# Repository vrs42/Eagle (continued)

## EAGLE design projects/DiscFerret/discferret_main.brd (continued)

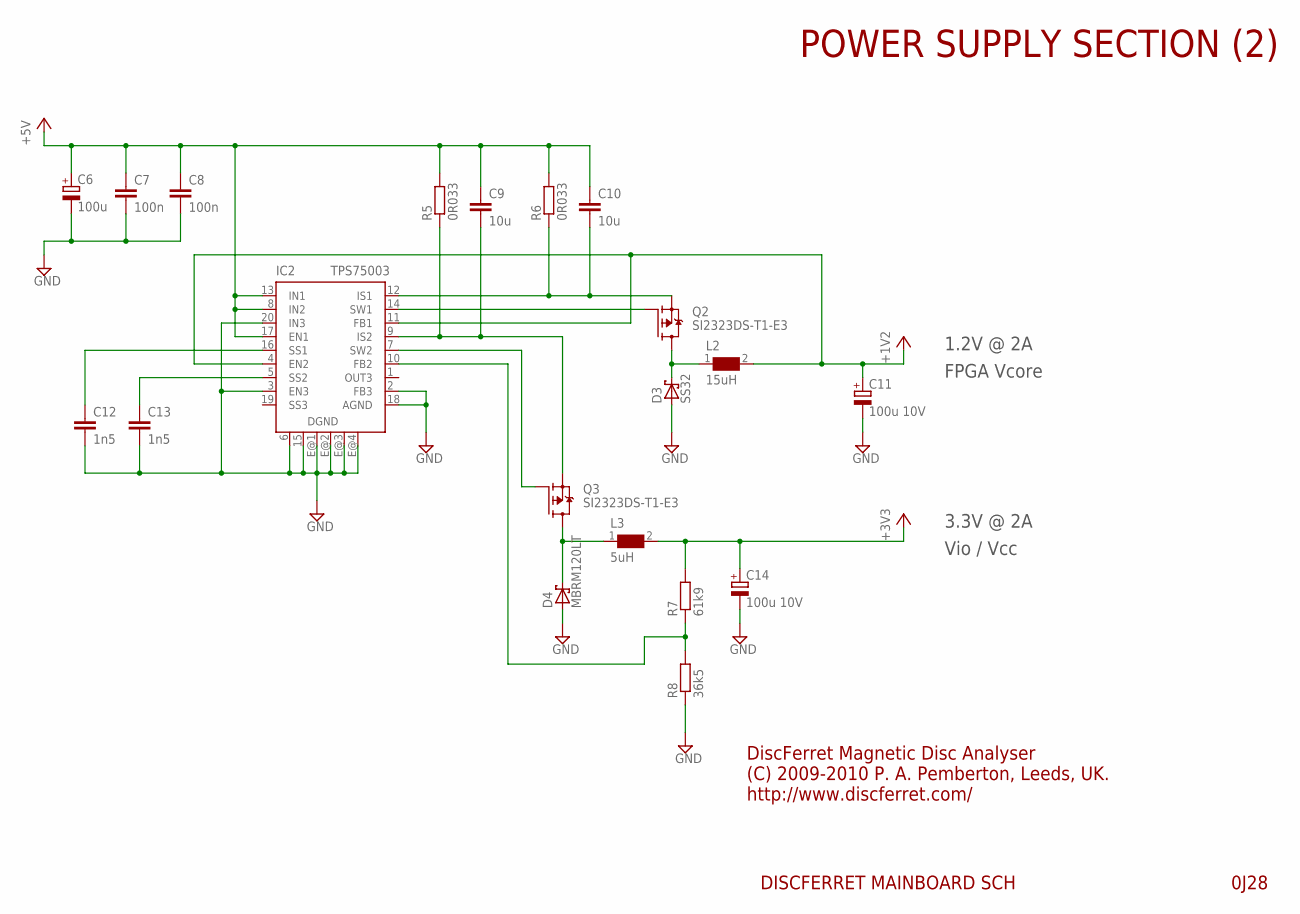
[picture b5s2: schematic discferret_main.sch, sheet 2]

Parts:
C6: 100u; SMC_D
C7, C8: 100n; C0805
C9, C10: 10u; C0805
C11, C14: 100u 10V; SMC_D
C12, C13: 1n5; C0805
D3: SS32; SMC
D4: MBRM120LT; POWERMITE_LARGEPAD
IC2: TPS75003; R-PQFP-N20
L2: 15uH; WE-TPC_XL/XLH
L3: 5uH; WE-TPC_XL/XLH
Q2, Q3: SI2323DS-T1-E3; SOT23
R5, R6: 0R033; R1206
R7: 61k9; R0805
R8: 36k5; R0603

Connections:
+1V2: C11.+, IC2.4 (EN2), IC2.11 (FB1), L2.2; also elsewhere on the board
+3V3: C14.+, L3.2, R7.2; also elsewhere on the board
+5V: C6.+, C7.1, C8.1, C9.1, C10.1, IC2.8 (IN2), IC2.13 (IN1), IC2.17 (EN1), R5.2, R6.2; also elsewhere on the board
GND: C6.-, C7.2, C8.2, C11.-, C12.2, C13.2, C14.-, D3.A, D4.2 (A), IC2.2 (FB3), IC2.3 (EN3), IC2.6 (DGND), IC2.15 (DGND), IC2.18 (AGND), IC2.20 (IN3), IC2.E@1 (DGND), IC2.E@2 (DGND), IC2.E@3 (DGND), IC2.E@4 (DGND), R8.1; also elsewhere on the board
unnamed: C9.2, IC2.9 (IS2), Q3.2 (S), R5.1
unnamed: C12.1, IC2.16 (SS1)
unnamed: C13.1, IC2.5 (SS2)
unnamed: C10.2, IC2.12 (IS1), Q2.2 (S), R6.1
unnamed: IC2.14 (SW1), Q2.1 (G)
unnamed: IC2.7 (SW2), Q3.1 (G)
unnamed: D3.C, L2.1, Q2.3 (D)
unnamed: D4.1 (C), L3.1, Q3.3 (D)
unnamed: IC2.10 (FB2), R7.1, R8.2

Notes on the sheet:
DiscFerret Magnetic Disc Analyser
0J28
DISCFERRET MAINBOARD SCH
(C) 2009-2010 P. A. Pemberton, Leeds, UK.
http://www.discferret.com/
POWER SUPPLY SECTION (2)
1.2V @ 2A
3.3V @ 2A
FPGA Vcore
Vio / Vcc

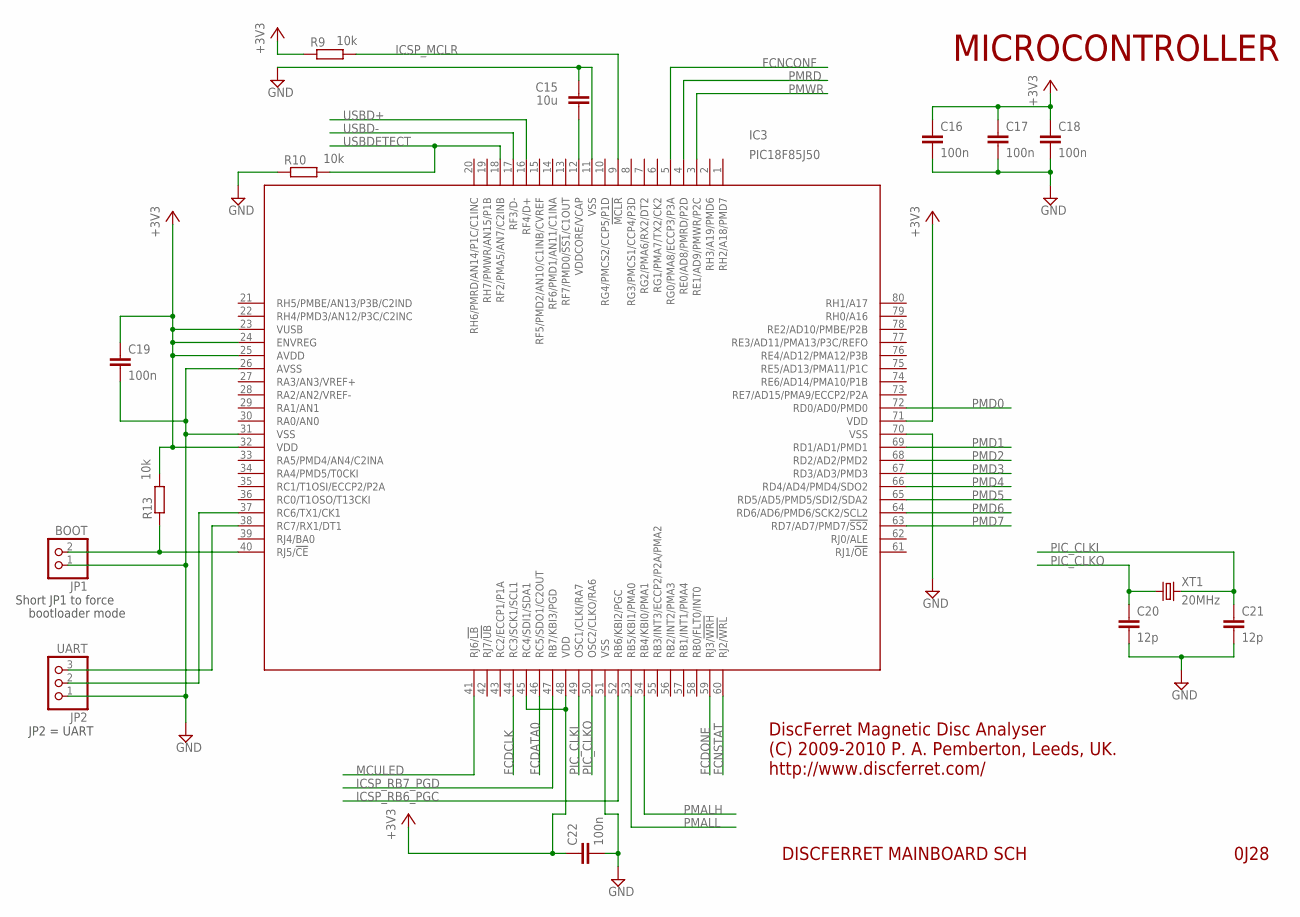
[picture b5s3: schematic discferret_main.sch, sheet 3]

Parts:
C15: 10u; C0805
C16, C17, C18, C19, C22: 100n; C0603
C20, C21: 12p; C0603
IC3: PIC18F85J50; TQFP80-12X12
JP1: BOOT; 1X02
JP2: UART; 1X03
R9, R10, R13: 10k; R0805
XT1: 20MHz; HC49/S

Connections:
+3V3: C16.1, C17.1, C18.1, C19.1, C22.1, IC3.23 (VUSB), IC3.24 (ENVREG), IC3.25 (AVDD), IC3.32 (VDD), IC3.45 (RC4/SDI1/SDA1), IC3.48 (VDD), IC3.71 (VDD), R9.1, R13.2; also elsewhere on the board
FCDATA0: IC3.46 (RC5/SDO1/C2OUT); also elsewhere on the board
FCDCLK: IC3.44 (RC3/SCK1/SCL1); also elsewhere on the board
FCDONE: IC3.59 (RJ3/!WRH); also elsewhere on the board
FCNCONF: IC3.5 (RG0/PMA8/ECCP3/P3A); also elsewhere on the board
FCNSTAT: IC3.60 (RJ2/!WRL); also elsewhere on the board
GND: C15.1, C16.2, C17.2, C18.2, C19.2, C20.2, C21.2, C22.2, IC3.11 (VSS), IC3.26 (AVSS), IC3.31 (VSS), IC3.51 (VSS), IC3.70 (VSS), JP1.1, JP2.1, R10.1; also elsewhere on the board
ICSP_MCLR: IC3.9 (!MCLR), R9.2; also elsewhere on the board
ICSP_RB6_PGC: IC3.52 (RB6/KBI2/PGC); also elsewhere on the board
ICSP_RB7_PGD: IC3.47 (RB7/KBI3/PGD); also elsewhere on the board
MCULED: IC3.41 (RJ6/!LB); also elsewhere on the board
unnamed: IC3.40 (RJ5/!CE), JP1.2, R13.1
unnamed: C15.2, IC3.12 (VDDCORE/VCAP)
unnamed: IC3.37 (RC6/TX1/CK1), JP2.2
unnamed: IC3.38 (RC7/RX1/DT1), JP2.3
PIC_CLKI: C21.1, IC3.49 (OSC1/CLKI/RA7), XT1.2
PIC_CLKO: C20.1, IC3.50 (OSC2/CLKO/RA6), XT1.1
PMALH: IC3.54 (RB4/KBI0/PMA1); also elsewhere on the board
PMALL: IC3.53 (RB5/KBI1/PMA0); also elsewhere on the board
PMD0: IC3.72 (RD0/AD0/PMD0); also elsewhere on the board
PMD1: IC3.69 (RD1/AD1/PMD1); also elsewhere on the board
PMD2: IC3.68 (RD2/AD2/PMD2); also elsewhere on the board
PMD3: IC3.67 (RD3/AD3/PMD3); also elsewhere on the board
PMD4: IC3.66 (RD4/AD4/PMD4/SDO2); also elsewhere on the board
PMD5: IC3.65 (RD5/AD5/PMD5/SDI2/SDA2); also elsewhere on the board
PMD6: IC3.64 (RD6/AD6/PMD6/SCK2/SCL2); also elsewhere on the board
PMD7: IC3.63 (RD7/AD7/PMD7/!SS2); also elsewhere on the board
PMRD: IC3.4 (RE0/AD8/PMRD/P2D); also elsewhere on the board
PMWR: IC3.3 (RE1/AD9/PMWR/P2C); also elsewhere on the board
USBD+: IC3.16 (RF4/D+); also elsewhere on the board
USBD-: IC3.17 (RF3/D-); also elsewhere on the board
USBDETECT: IC3.18 (RF2/PMA5/AN7/C2INB), R10.2; also elsewhere on the board

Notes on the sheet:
DiscFerret Magnetic Disc Analyser
0J28
DISCFERRET MAINBOARD SCH
(C) 2009-2010 P. A. Pemberton, Leeds, UK.
http://www.discferret.com/
MICROCONTROLLER
Short JP1 to force
bootloader mode
JP2 = UART

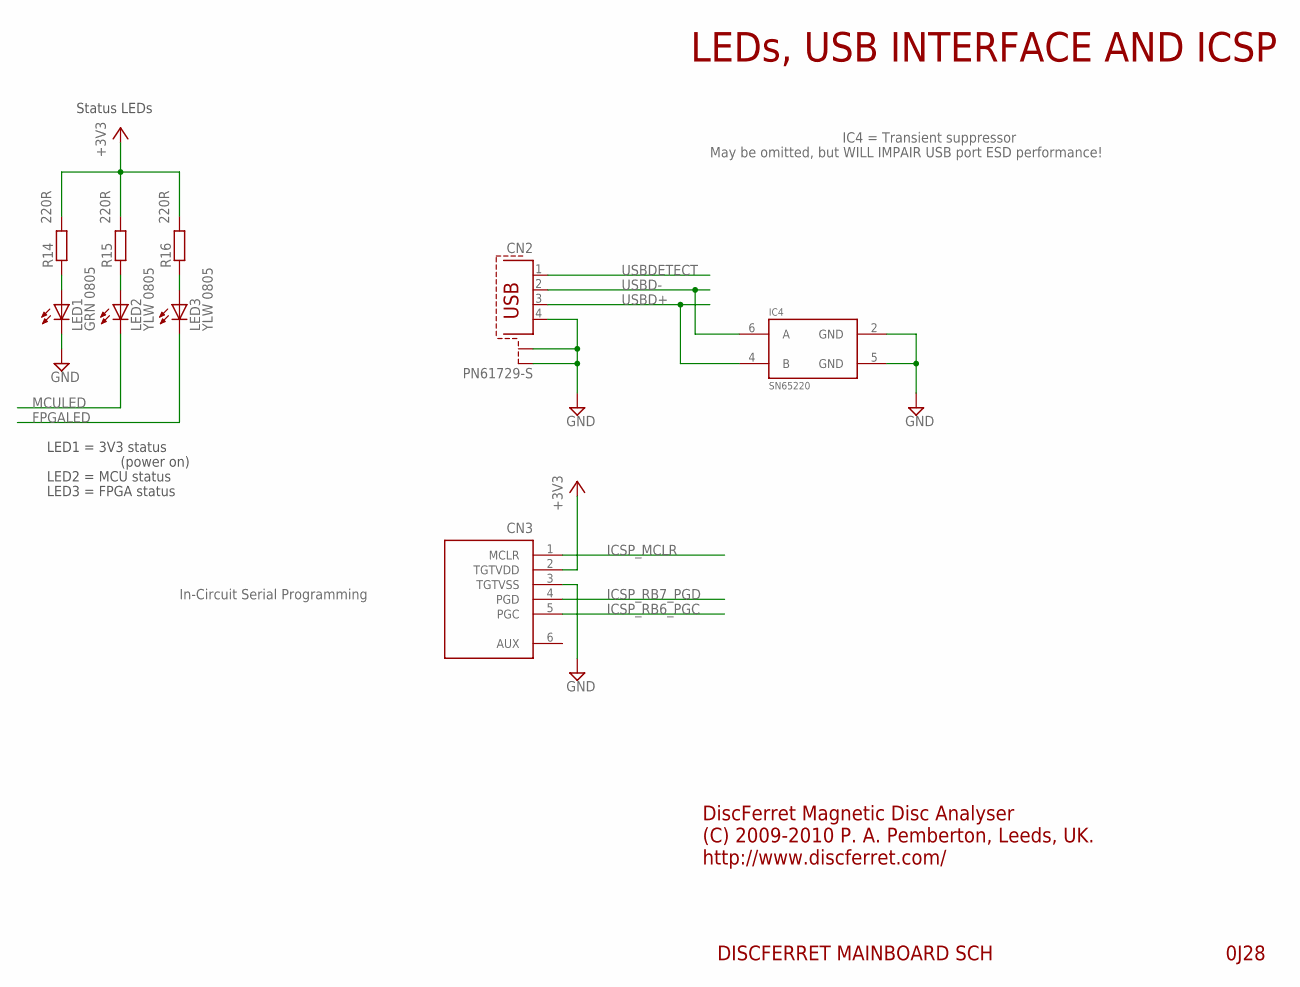
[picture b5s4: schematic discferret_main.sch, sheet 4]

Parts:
CN2: PN61729-S
CN3: ICSPSMD; ICSP_SMD
IC4: SN65220; SOT23-6L
LED1: GRN 0805; CHIPLED_0805
LED2, LED3: YLW 0805; CHIPLED_0805
R14, R15, R16: 220R; R0805

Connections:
+3V3: CN3.2 (TGTVDD), R14.2, R15.2, R16.2; also elsewhere on the board
FPGALED: LED3.C; also elsewhere on the board
GND: CN2.4, CN2.S1, CN2.S2, CN3.3 (TGTVSS), IC4.2 (GND), IC4.5 (GND), LED1.C; also elsewhere on the board
ICSP_MCLR: CN3.1 (MCLR); also elsewhere on the board
ICSP_RB6_PGC: CN3.5 (PGC); also elsewhere on the board
ICSP_RB7_PGD: CN3.4 (PGD); also elsewhere on the board
MCULED: LED2.C; also elsewhere on the board
unnamed: LED1.A, R14.1
unnamed: LED2.A, R15.1
unnamed: LED3.A, R16.1
USBD+: CN2.3, IC4.4 (B); also elsewhere on the board
USBD-: CN2.2, IC4.6 (A); also elsewhere on the board
USBDETECT: CN2.1; also elsewhere on the board

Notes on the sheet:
DiscFerret Magnetic Disc Analyser
0J28
DISCFERRET MAINBOARD SCH
(C) 2009-2010 P. A. Pemberton, Leeds, UK.
http://www.discferret.com/
LEDs, USB INTERFACE AND ICSP
IC4 = Transient suppressor
May be omitted, but WILL IMPAIR USB port ESD performance!
In-Circuit Serial Programming
LED1 = 3V3 status
(power on)
LED2 = MCU status
LED3 = FPGA status
Status LEDs

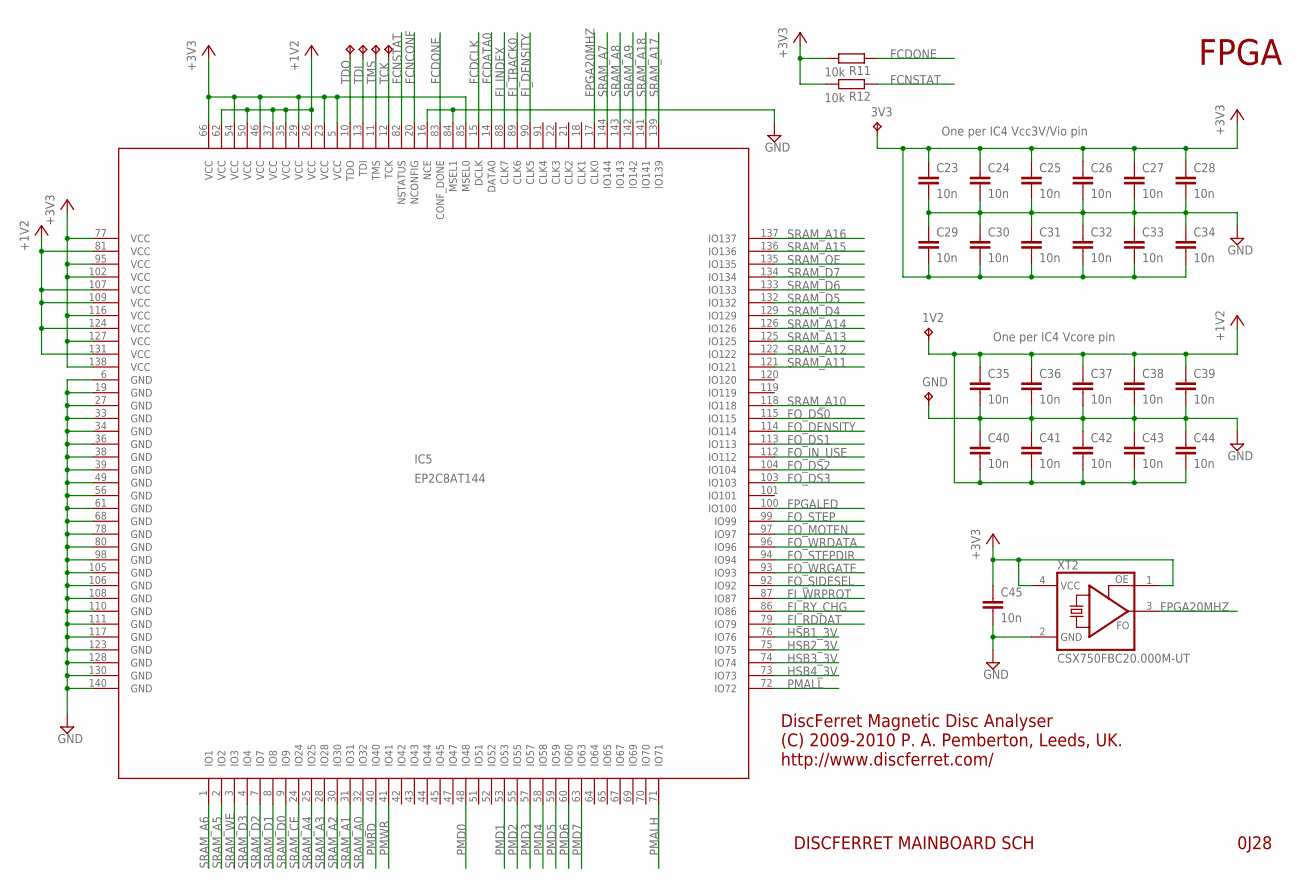
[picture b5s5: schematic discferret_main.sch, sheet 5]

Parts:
1V2, 3V3: TPB1,27; B1,27
C23, C24, C25, C26, C27, C28, C29, C30, C31, C32, C33, C34, C35, C36, C37, C38, C39, C40, C41, C42, C43, C44, C45: 10n; C0603
GND: TPB1,27; B1,27
IC5: EP2C8AT144; TQFP144
R11, R12: 10k; R0805
TCK: TPB1,27; B1,27
TDI: TPB1,27; B1,27
TDO: TPB1,27; B1,27
TMS: TPB1,27; B1,27
XT2: CSX750FBC20.000M-UT; CSX750F

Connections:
+1V2: 1V2.TP, C35.1, C36.1, C37.1, C38.1, C39.1, C40.2, C41.2, C42.2, C43.2, C44.2, IC5.26 (VCC), IC5.35 (VCC), IC5.37 (VCC), IC5.50 (VCC), IC5.62 (VCC), IC5.81 (VCC), IC5.107 (VCC), IC5.109 (VCC), IC5.124 (VCC), IC5.131 (VCC); also elsewhere on the board
+3V3: 3V3.TP, C23.1, C24.1, C25.1, C26.1, C27.1, C28.1, C29.2, C30.2, C31.2, C32.2, C33.2, C34.2, C45.1, IC5.5 (VCC), IC5.23 (VCC), IC5.29 (VCC), IC5.46 (VCC), IC5.54 (VCC), IC5.66 (VCC), IC5.77 (VCC), IC5.85 (MSEL0), IC5.95 (VCC), IC5.102 (VCC), IC5.116 (VCC), IC5.127 (VCC), IC5.138 (VCC), R11.2, R12.2, XT2.1 (OE), XT2.4 (VCC); also elsewhere on the board
FCDATA0: IC5.14 (DATA0); also elsewhere on the board
FCDCLK: IC5.15 (DCLK); also elsewhere on the board
FCDONE: IC5.83 (CONF_DONE), R11.1; also elsewhere on the board
FCNCONF: IC5.20 (NCONFIG); also elsewhere on the board
FCNSTAT: IC5.82 (NSTATUS), R12.1; also elsewhere on the board
FI_DENSITY: IC5.90 (CLK5); also elsewhere on the board
FI_INDEX: IC5.88 (CLK7); also elsewhere on the board
FI_RDDAT: IC5.79 (IO79); also elsewhere on the board
FI_RY_CHG: IC5.86 (IO86); also elsewhere on the board
FI_TRACK0: IC5.89 (CLK6); also elsewhere on the board
FI_WRPROT: IC5.87 (IO87); also elsewhere on the board
FO_DENSITY: IC5.114 (IO114); also elsewhere on the board
FO_DS0: IC5.115 (IO115); also elsewhere on the board
FO_DS1: IC5.113 (IO113); also elsewhere on the board
FO_DS2: IC5.104 (IO104); also elsewhere on the board
FO_DS3: IC5.103 (IO103); also elsewhere on the board
FO_IN_USE: IC5.112 (IO112); also elsewhere on the board
FO_MOTEN: IC5.97 (IO97); also elsewhere on the board
FO_SIDESEL: IC5.92 (IO92); also elsewhere on the board
FO_STEP: IC5.99 (IO99); also elsewhere on the board
FO_STEPDIR: IC5.94 (IO94); also elsewhere on the board
FO_WRDATA: IC5.96 (IO96); also elsewhere on the board
FO_WRGATE: IC5.93 (IO93); also elsewhere on the board
FPGA20MHZ: IC5.17 (CLK0), XT2.3 (FO)
FPGALED: IC5.100 (IO100); also elsewhere on the board
GND: C23.2, C24.2, C25.2, C26.2, C27.2, C28.2, C29.1, C30.1, C31.1, C32.1, C33.1, C34.1, C35.2, C36.2, C37.2, C38.2, C39.2, C40.1, C41.1, C42.1, C43.1, C44.1, C45.2, GND.TP, IC5.6 (GND), IC5.16 (NCE), IC5.19 (GND), IC5.27 (GND), IC5.33 (GND), IC5.34 (GND), IC5.36 (GND), IC5.38 (GND), IC5.39 (GND), IC5.49 (GND), IC5.56 (GND), IC5.61 (GND), IC5.68 (GND), IC5.78 (GND), IC5.80 (GND), IC5.84 (MSEL1), IC5.98 (GND), IC5.105 (GND), IC5.106 (GND), IC5.108 (GND), IC5.110 (GND), IC5.111 (GND), IC5.117 (GND), IC5.123 (GND), IC5.128 (GND), IC5.130 (GND), IC5.140 (GND), XT2.2 (GND); also elsewhere on the board
HSB1_3V: IC5.76 (IO76); also elsewhere on the board
HSB2_3V: IC5.75 (IO75); also elsewhere on the board
HSB3_3V: IC5.74 (IO74); also elsewhere on the board
HSB4_3V: IC5.73 (IO73); also elsewhere on the board
PMALH: IC5.71 (IO71); also elsewhere on the board
PMALL: IC5.72 (IO72); also elsewhere on the board
PMD0: IC5.48 (IO48); also elsewhere on the board
PMD1: IC5.53 (IO53); also elsewhere on the board
PMD2: IC5.55 (IO55); also elsewhere on the board
PMD3: IC5.57 (IO57); also elsewhere on the board
PMD4: IC5.58 (IO58); also elsewhere on the board
PMD5: IC5.59 (IO59); also elsewhere on the board
PMD6: IC5.60 (IO60); also elsewhere on the board
PMD7: IC5.63 (IO63); also elsewhere on the board
PMRD: IC5.40 (IO40); also elsewhere on the board
PMWR: IC5.41 (IO41); also elsewhere on the board
SRAM_A0: IC5.32 (IO32); also elsewhere on the board
SRAM_A1: IC5.31 (IO31); also elsewhere on the board
SRAM_A2: IC5.30 (IO30); also elsewhere on the board
SRAM_A3: IC5.28 (IO28); also elsewhere on the board
SRAM_A4: IC5.25 (IO25); also elsewhere on the board
SRAM_A5: IC5.2 (IO2); also elsewhere on the board
SRAM_A6: IC5.1 (IO1); also elsewhere on the board
SRAM_A7: IC5.144 (IO144); also elsewhere on the board
SRAM_A8: IC5.143 (IO143); also elsewhere on the board
SRAM_A9: IC5.142 (IO142); also elsewhere on the board
SRAM_A10: IC5.118 (IO118); also elsewhere on the board
SRAM_A11: IC5.121 (IO121); also elsewhere on the board
SRAM_A12: IC5.122 (IO122); also elsewhere on the board
SRAM_A13: IC5.125 (IO125); also elsewhere on the board
SRAM_A14: IC5.126 (IO126); also elsewhere on the board
SRAM_A15: IC5.136 (IO136); also elsewhere on the board
SRAM_A16: IC5.137 (IO137); also elsewhere on the board
SRAM_A17: IC5.139 (IO139); also elsewhere on the board
SRAM_A18: IC5.141 (IO141); also elsewhere on the board
SRAM_CE: IC5.24 (IO24); also elsewhere on the board
SRAM_D0: IC5.9 (IO9); also elsewhere on the board
SRAM_D1: IC5.8 (IO8); also elsewhere on the board
SRAM_D2: IC5.7 (IO7); also elsewhere on the board
SRAM_D3: IC5.4 (IO4); also elsewhere on the board
SRAM_D4: IC5.129 (IO129); also elsewhere on the board
SRAM_D5: IC5.132 (IO132); also elsewhere on the board
SRAM_D6: IC5.133 (IO133); also elsewhere on the board
SRAM_D7: IC5.134 (IO134); also elsewhere on the board
SRAM_OE: IC5.135 (IO135); also elsewhere on the board
SRAM_WE: IC5.3 (IO3); also elsewhere on the board
TCK: IC5.12 (TCK), TCK.TP
TDI: IC5.13 (TDI), TDI.TP
TDO: IC5.10 (TDO), TDO.TP
TMS: IC5.11 (TMS), TMS.TP

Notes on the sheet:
DiscFerret Magnetic Disc Analyser
0J28
DISCFERRET MAINBOARD SCH
(C) 2009-2010 P. A. Pemberton, Leeds, UK.
http://www.discferret.com/
FPGA
One per IC4 Vcc3V/Vio pin
One per IC4 Vcore pin

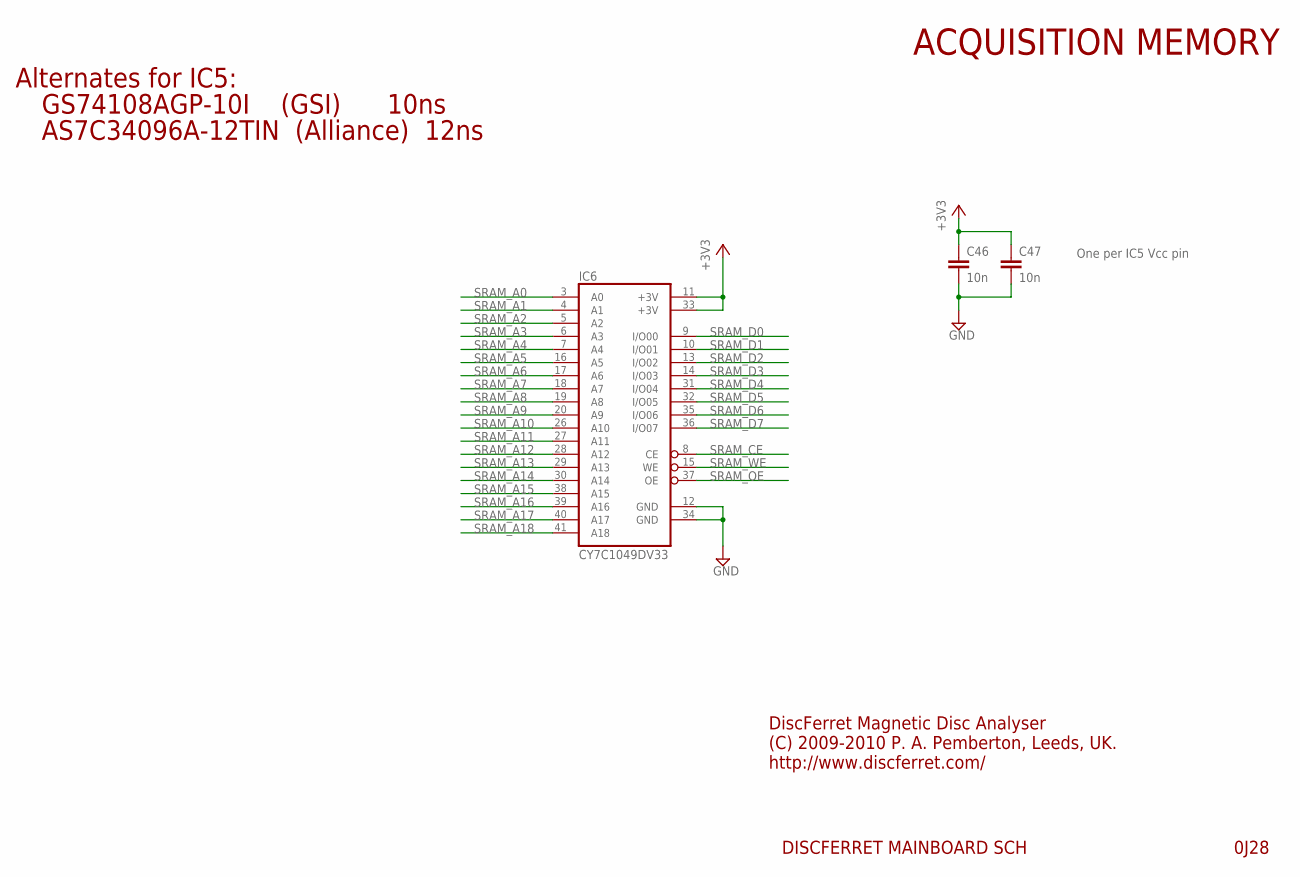
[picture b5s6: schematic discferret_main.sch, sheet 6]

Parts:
C46, C47: 10n; C0603
IC6: CY7C1049DV33; TSOPII-Z44

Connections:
+3V3: C46.1, C47.1, IC6.11 (+3V), IC6.33 (+3V); also elsewhere on the board
GND: C46.2, C47.2, IC6.12 (GND), IC6.34 (GND); also elsewhere on the board
SRAM_A0: IC6.3 (A0); also elsewhere on the board
SRAM_A1: IC6.4 (A1); also elsewhere on the board
SRAM_A2: IC6.5 (A2); also elsewhere on the board
SRAM_A3: IC6.6 (A3); also elsewhere on the board
SRAM_A4: IC6.7 (A4); also elsewhere on the board
SRAM_A5: IC6.16 (A5); also elsewhere on the board
SRAM_A6: IC6.17 (A6); also elsewhere on the board
SRAM_A7: IC6.18 (A7); also elsewhere on the board
SRAM_A8: IC6.19 (A8); also elsewhere on the board
SRAM_A9: IC6.20 (A9); also elsewhere on the board
SRAM_A10: IC6.26 (A10); also elsewhere on the board
SRAM_A11: IC6.27 (A11); also elsewhere on the board
SRAM_A12: IC6.28 (A12); also elsewhere on the board
SRAM_A13: IC6.29 (A13); also elsewhere on the board
SRAM_A14: IC6.30 (A14); also elsewhere on the board
SRAM_A15: IC6.38 (A15); also elsewhere on the board
SRAM_A16: IC6.39 (A16); also elsewhere on the board
SRAM_A17: IC6.40 (A17); also elsewhere on the board
SRAM_A18: IC6.41 (A18); also elsewhere on the board
SRAM_CE: IC6.8 (CE); also elsewhere on the board
SRAM_D0: IC6.9 (I/O00); also elsewhere on the board
SRAM_D1: IC6.10 (I/O01); also elsewhere on the board
SRAM_D2: IC6.13 (I/O02); also elsewhere on the board
SRAM_D3: IC6.14 (I/O03); also elsewhere on the board
SRAM_D4: IC6.31 (I/O04); also elsewhere on the board
SRAM_D5: IC6.32 (I/O05); also elsewhere on the board
SRAM_D6: IC6.35 (I/O06); also elsewhere on the board
SRAM_D7: IC6.36 (I/O07); also elsewhere on the board
SRAM_OE: IC6.37 (OE); also elsewhere on the board
SRAM_WE: IC6.15 (WE); also elsewhere on the board

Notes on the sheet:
DiscFerret Magnetic Disc Analyser
0J28
DISCFERRET MAINBOARD SCH
(C) 2009-2010 P. A. Pemberton, Leeds, UK.
http://www.discferret.com/
ACQUISITION MEMORY
Alternates for IC5:
GS74108AGP-10I (GSI) 10ns
AS7C34096A-12TIN (Alliance) 12ns
One per IC5 Vcc pin

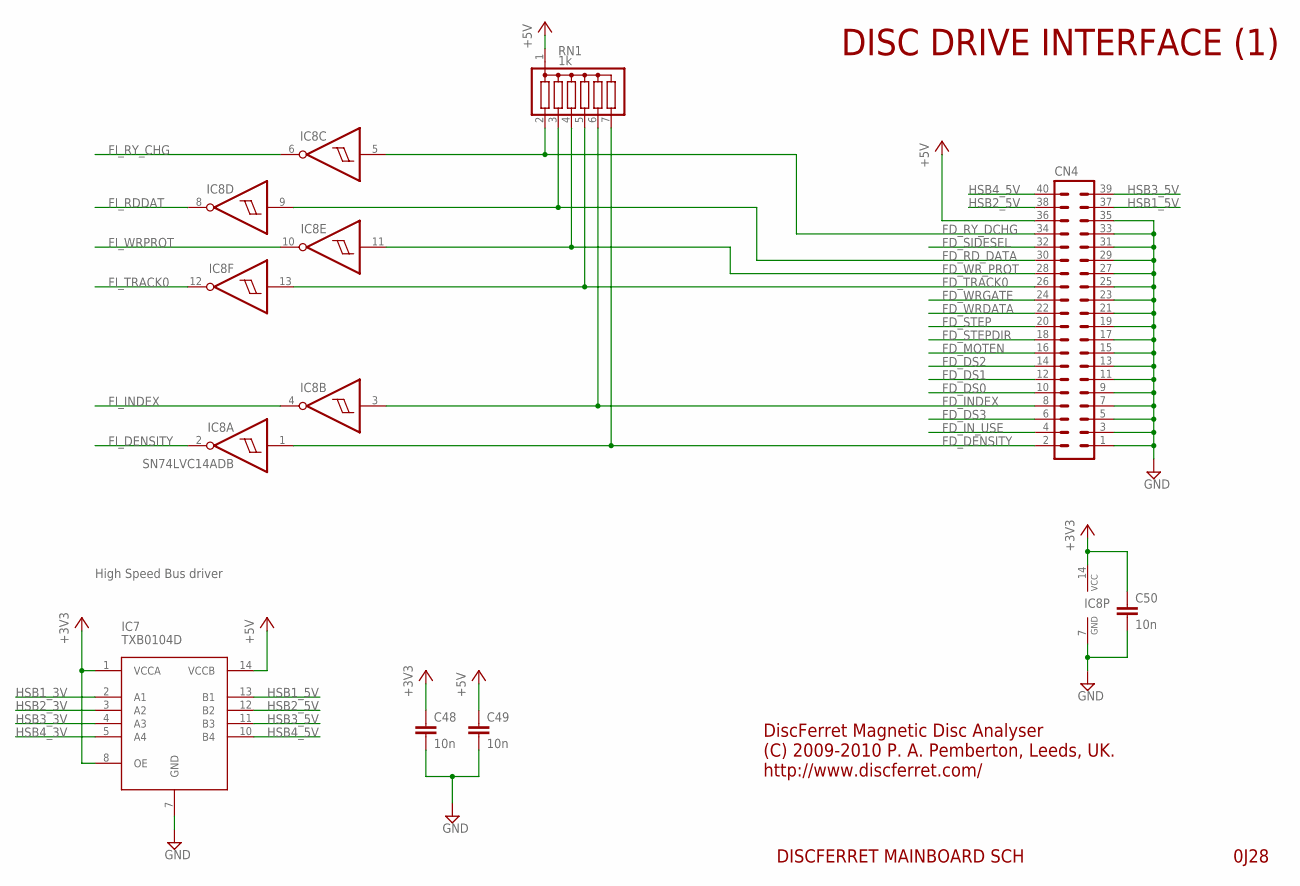
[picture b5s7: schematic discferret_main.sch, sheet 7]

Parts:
C48, C49, C50: 10n; C0603
CN4: 40H
IC7: TXB0104D; SO14
IC8: SN74LVC14ADB; SSOP14
RN1: 1k; SIL7

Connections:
+3V3: C48.1, C50.1, IC7.1 (VCCA), IC7.8 (OE), IC8.14 (VCC); also elsewhere on the board
+5V: C49.1, CN4.36, IC7.14 (VCCB), RN1.1; also elsewhere on the board
FD_DENSITY: CN4.2, IC8.1 (I), RN1.7; also elsewhere on the board
FD_DS0: CN4.10; also elsewhere on the board
FD_DS1: CN4.12; also elsewhere on the board
FD_DS2: CN4.14; also elsewhere on the board
FD_DS3: CN4.6; also elsewhere on the board
FD_INDEX: CN4.8, IC8.3 (I), RN1.6
FD_IN_USE: CN4.4; also elsewhere on the board
FD_MOTEN: CN4.16; also elsewhere on the board
FD_RD_DATA: CN4.30, IC8.9 (I), RN1.3
FD_RY_DCHG: CN4.34, IC8.5 (I), RN1.2
FD_SIDESEL: CN4.32; also elsewhere on the board
FD_STEP: CN4.20; also elsewhere on the board
FD_STEPDIR: CN4.18; also elsewhere on the board
FD_TRACK0: CN4.26, IC8.13 (I), RN1.5
FD_WRDATA: CN4.22; also elsewhere on the board
FD_WRGATE: CN4.24; also elsewhere on the board
FD_WR_PROT: CN4.28, IC8.11 (I), RN1.4
FI_DENSITY: IC8.2 (O); also elsewhere on the board
FI_INDEX: IC8.4 (O); also elsewhere on the board
FI_RDDAT: IC8.8 (O); also elsewhere on the board
FI_RY_CHG: IC8.6 (O); also elsewhere on the board
FI_TRACK0: IC8.12 (O); also elsewhere on the board
FI_WRPROT: IC8.10 (O); also elsewhere on the board
GND: C48.2, C49.2, C50.2, CN4.1, CN4.3, CN4.5, CN4.7, CN4.9, CN4.11, CN4.13, CN4.15, CN4.17, CN4.19, CN4.21, CN4.23, CN4.25, CN4.27, CN4.29, CN4.31, CN4.33, CN4.35, IC7.7 (GND), IC8.7 (GND); also elsewhere on the board
HSB1_3V: IC7.2 (A1); also elsewhere on the board
HSB1_5V: CN4.37, IC7.13 (B1)
HSB2_3V: IC7.3 (A2); also elsewhere on the board
HSB2_5V: CN4.38, IC7.12 (B2)
HSB3_3V: IC7.4 (A3); also elsewhere on the board
HSB3_5V: CN4.39, IC7.11 (B3)
HSB4_3V: IC7.5 (A4); also elsewhere on the board
HSB4_5V: CN4.40, IC7.10 (B4)

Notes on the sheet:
DiscFerret Magnetic Disc Analyser
0J28
DISCFERRET MAINBOARD SCH
(C) 2009-2010 P. A. Pemberton, Leeds, UK.
http://www.discferret.com/
DISC DRIVE INTERFACE (1)
High Speed Bus driver

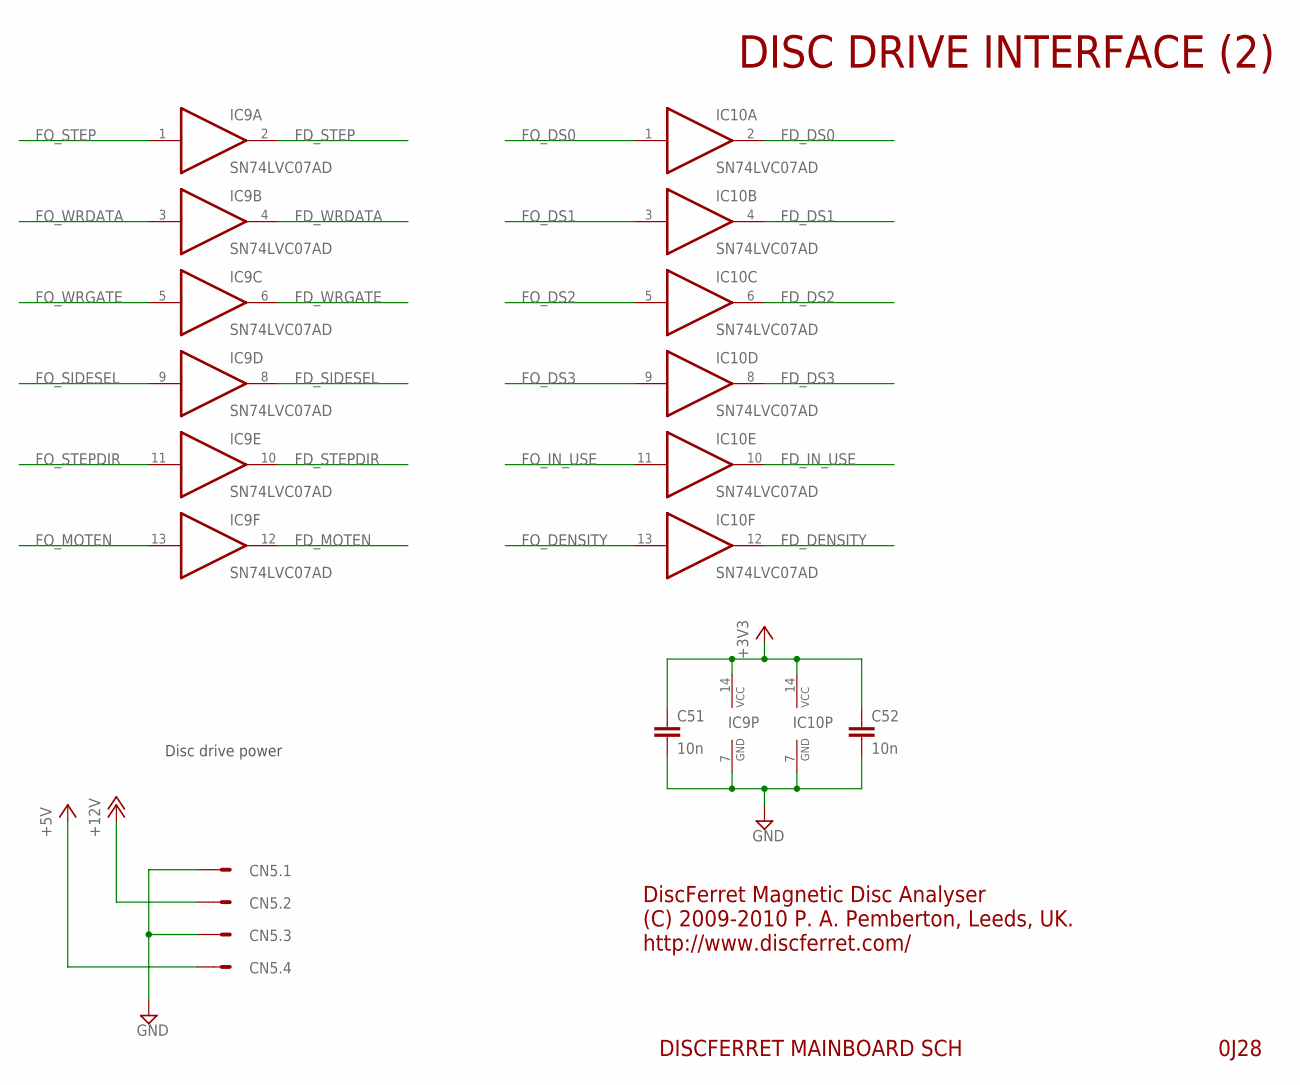
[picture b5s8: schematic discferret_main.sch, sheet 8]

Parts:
C51, C52: 10n; C0603
CN5: 2X2-A; 3-794618-4
IC9, IC10: SN74LVC07AD; SO14

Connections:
+3V3: C51.1, C52.1, IC9.14 (VCC), IC10.14 (VCC); also elsewhere on the board
+5V: CN5.4; also elsewhere on the board
+12V: CN5.2; also elsewhere on the board
FD_DENSITY: IC10.12 (O); also elsewhere on the board
FD_DS0: IC10.2 (O); also elsewhere on the board
FD_DS1: IC10.4 (O); also elsewhere on the board
FD_DS2: IC10.6 (O); also elsewhere on the board
FD_DS3: IC10.8 (O); also elsewhere on the board
FD_IN_USE: IC10.10 (O); also elsewhere on the board
FD_MOTEN: IC9.12 (O); also elsewhere on the board
FD_SIDESEL: IC9.8 (O); also elsewhere on the board
FD_STEP: IC9.2 (O); also elsewhere on the board
FD_STEPDIR: IC9.10 (O); also elsewhere on the board
FD_WRDATA: IC9.4 (O); also elsewhere on the board
FD_WRGATE: IC9.6 (O); also elsewhere on the board
FO_DENSITY: IC10.13 (I); also elsewhere on the board
FO_DS0: IC10.1 (I); also elsewhere on the board
FO_DS1: IC10.3 (I); also elsewhere on the board
FO_DS2: IC10.5 (I); also elsewhere on the board
FO_DS3: IC10.9 (I); also elsewhere on the board
FO_IN_USE: IC10.11 (I); also elsewhere on the board
FO_MOTEN: IC9.13 (I); also elsewhere on the board
FO_SIDESEL: IC9.9 (I); also elsewhere on the board
FO_STEP: IC9.1 (I); also elsewhere on the board
FO_STEPDIR: IC9.11 (I); also elsewhere on the board
FO_WRDATA: IC9.3 (I); also elsewhere on the board
FO_WRGATE: IC9.5 (I); also elsewhere on the board
GND: C51.2, C52.2, CN5.1, CN5.3, IC9.7 (GND), IC10.7 (GND); also elsewhere on the board

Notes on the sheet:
DiscFerret Magnetic Disc Analyser
0J28
DISCFERRET MAINBOARD SCH
(C) 2009-2010 P. A. Pemberton, Leeds, UK.
http://www.discferret.com/
DISC DRIVE INTERFACE (2)
Disc drive power

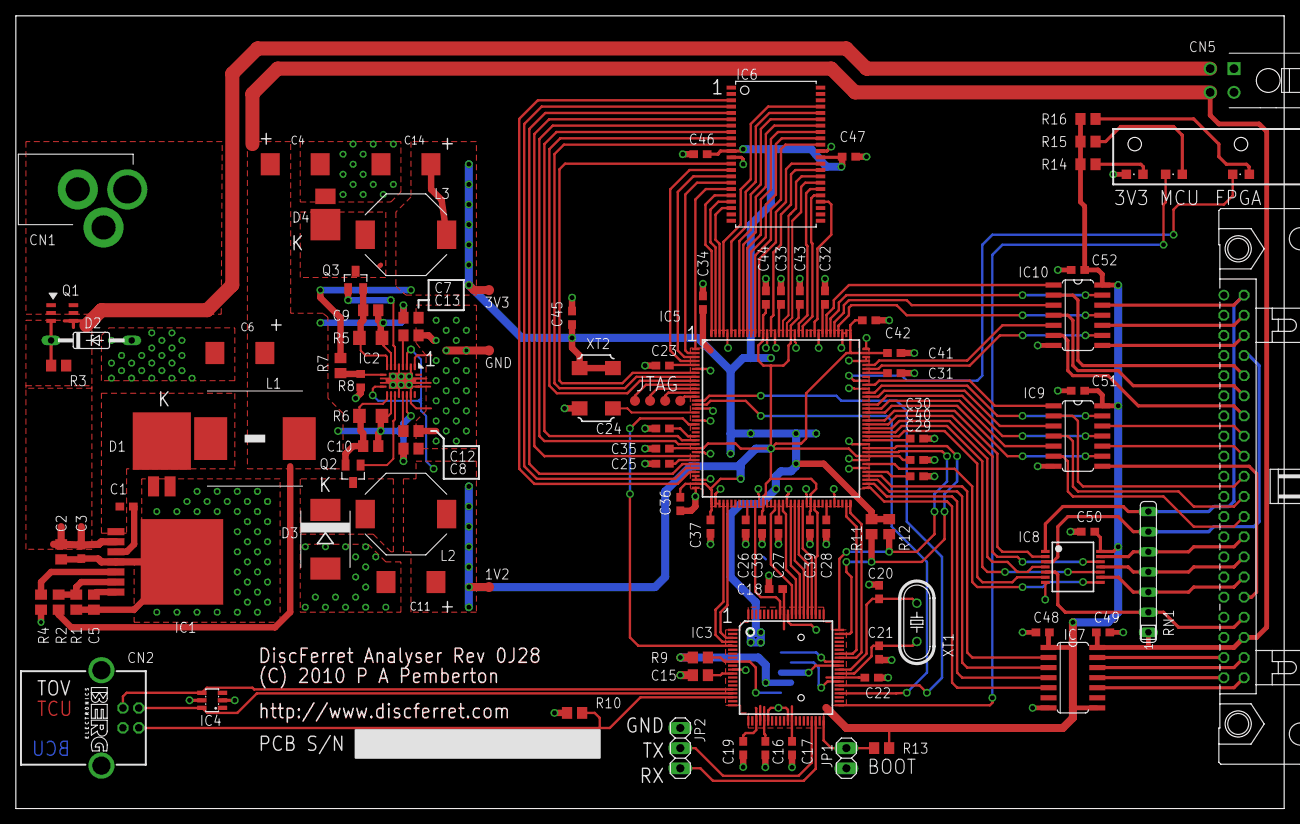
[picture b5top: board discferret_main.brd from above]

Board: 2 copper layers, 160.0 x 100.0 mm, 108 parts (1 on the bottom side), 133 nets.
